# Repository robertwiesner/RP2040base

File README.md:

A small example for a RP2040 board with I2C (LCD display), LED blinking and some GPIOs

GPIO 0 - 3: LED

J4: 
GPIO6: GPIO/I2C1_SDA
GPIO7: GPIO/I2C1_SCL
GPIO8: GPIO/UART1_TX/I2C0_SDA/SPI1_RX
GPIO9: GPIO/UART1_RX/I2C0_SCL/SPI1_CSn
GPIO10: GPIO/I2C1_SDA/SPI1_SCK
GPIO11: GPIO/I2C1_SCL/SPI1_TX
GPIO12: GPIO/UART0_TX/I2C0_SDA/SPI1_RX
GPIO13: GPIO/UART0_RX/I2C0_SCL/SPI1_CSn

J3:
I2C0, GND, and 3.3V

HTTP Links and cloning:
* https://github.com/raspberrypi/picotool
* https://github.com/raspberrypi/pico-sdk
* https://github.com/raspberrypi/pico-extras

| End Symb |  |
| --- | --- |
| PICO_SDK_PATH | point to <path>/pico-sdk |
| PICO_EXTRAS_PATH | point to <path>/pico-extras |

Clone the pico repositories:
* https://github.com/raspberrypi/pico-sdk.git
* https://github.com/raspberrypi/pico-extras.git
* Install the picotool repository

How to build:
* First time:
 * make build directory in the source directory: mkdir build
 * chdir build
 * cmake ..
* every time
 * Change into build directory
 * Start build using "make"
 * install to pico: picotool load test.uf2 && picotool reboot

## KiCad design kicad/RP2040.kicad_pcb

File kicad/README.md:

This directory conteains the schematics and layout data for the C example program.

About the board:
1. Using a USB type C connector for power and USB 2.0 connection
2. I2C connector for LEC display
3. 4 * ANALOG input with 1:10 power divider for the RP2040 ADC input
4. Accessible GPIO 6 - 13
5. 2*5V (USB) and 2*3.3V connector
6. GPIO 0-3 connected to LED
7. 10-pin, 1.27mm SWD connector

The Part numbers in the schemetaics match the JLCPCB (not sponsered) order code.

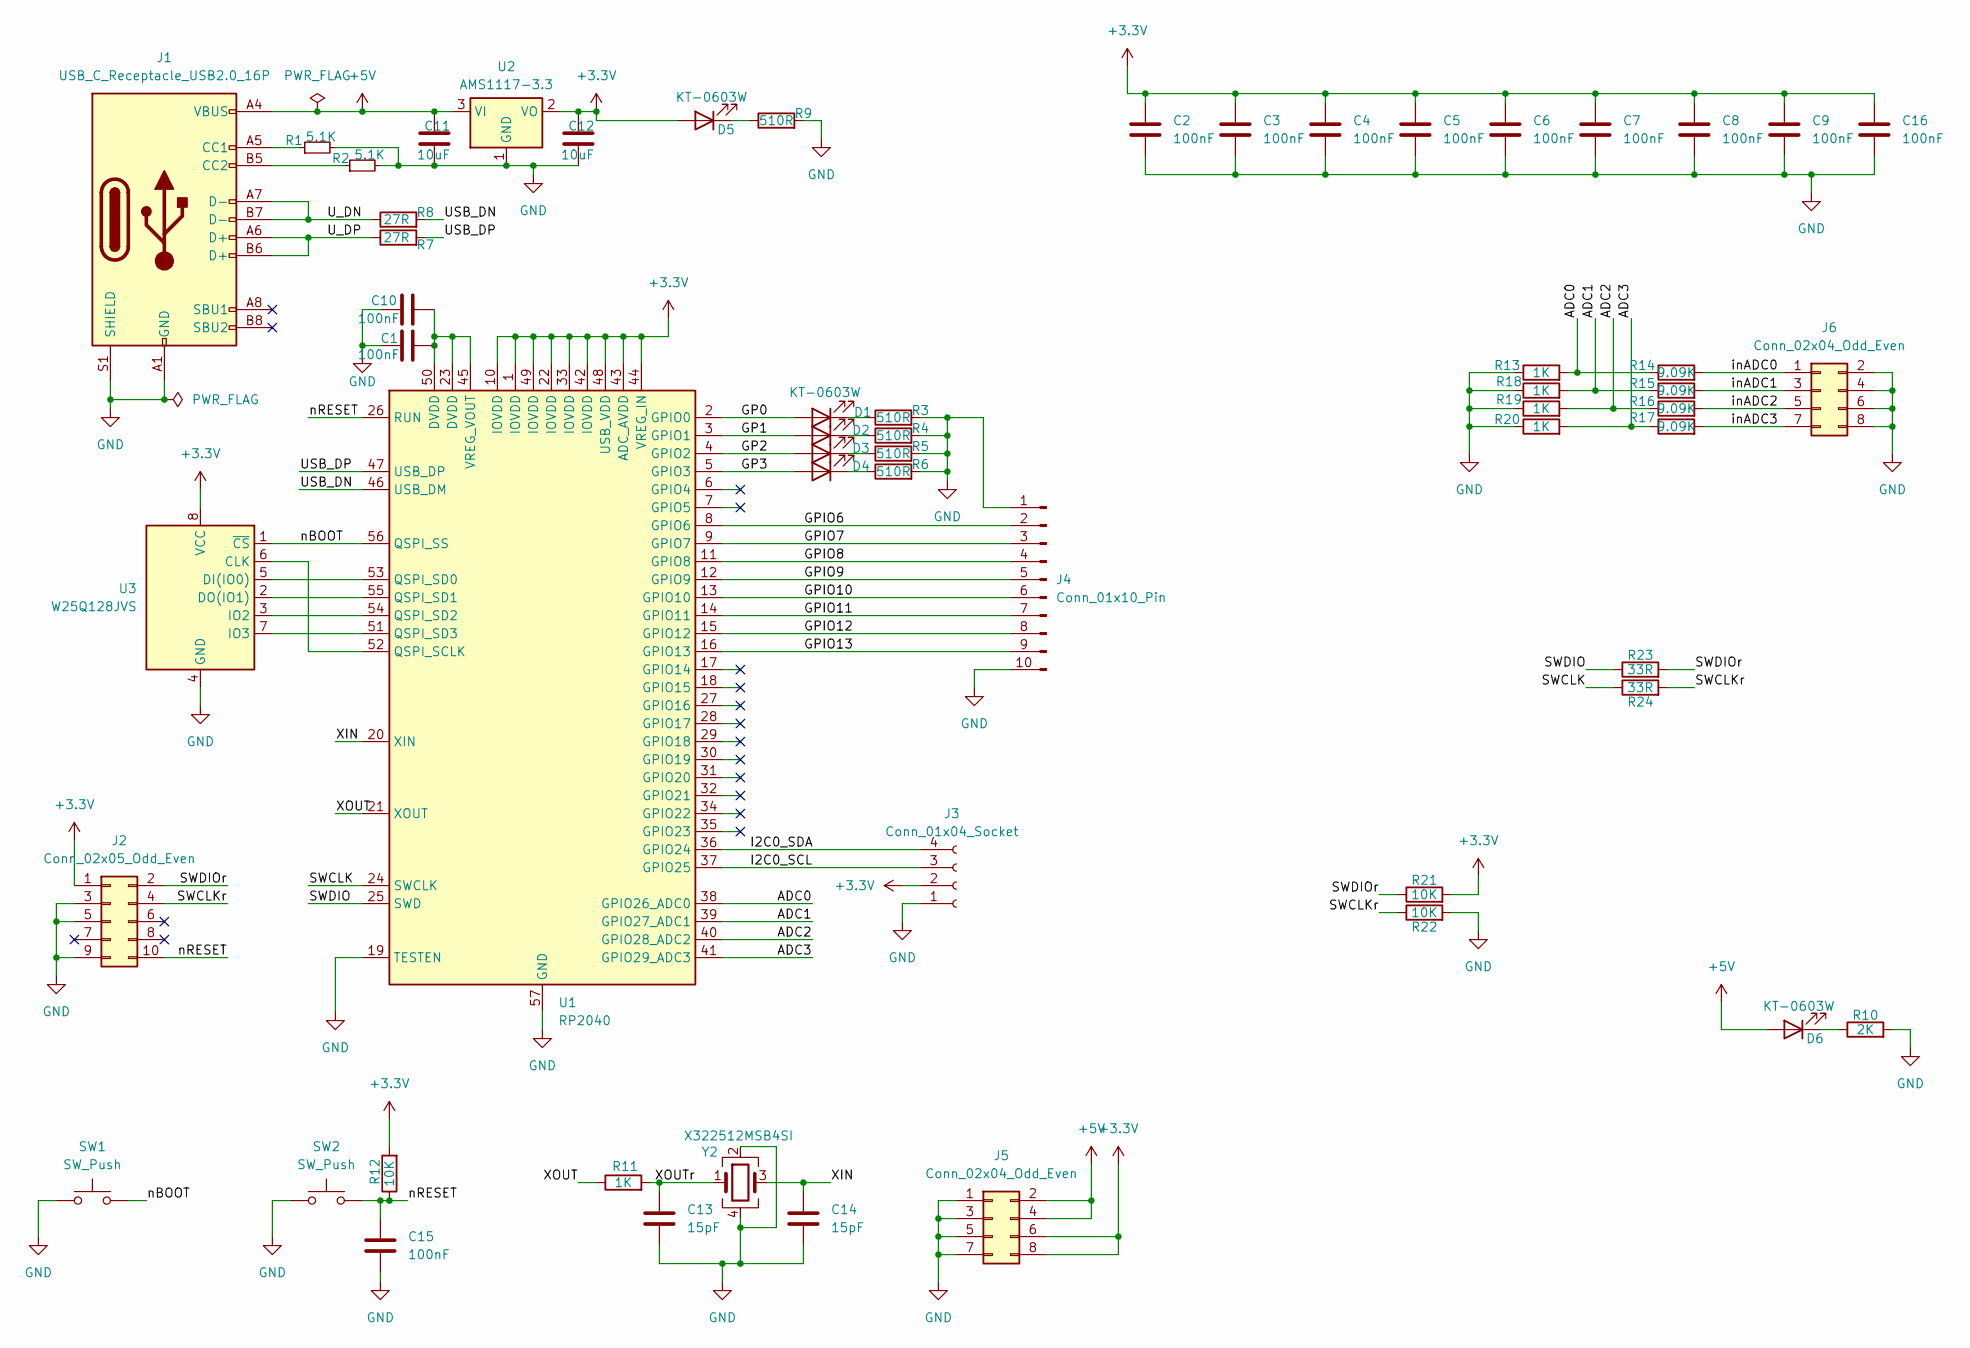
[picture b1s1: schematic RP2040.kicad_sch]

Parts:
C1, C2, C3, C4, C5, C6, C7, C8, C9, C10, C15, C16: 100nF; C_0402_1005Metric
C11, C12: 10uF; C_0603_1608Metric; LCSC C19702
C13, C14: 15pF; C_0402_1005Metric
D1, D2, D3, D4, D5, D6: KT-0603W; LED_0603_1608Metric
J1: USB_C_Receptacle_USB2.0_16P; USB_C_Receptacle_G-Switch_GT-USB-7010ASV
J2: Conn_02x05_Odd_Even; PinHeader_2x05_P1.27mm_Vertical_SMD; LCSC C5160761
J3: Conn_01x04_Socket; PinSocket_1x04_P2.54mm_Vertical
J4: Conn_01x10_Pin; PinSocket_1x10_P2.54mm_Vertical
J5, J6: Conn_02x04_Odd_Even; PinHeader_2x04_P2.54mm_Vertical
R1, R2: 5.1K; R_0402_1005Metric
R3, R4, R5, R6, R9: 510R; R_0402_1005Metric
R7, R8: 27R; R_0402_1005Metric
R10: 2K; R_0402_1005Metric
R11, R13, R18, R19, R20: 1K; R_0402_1005Metric
R12, R21, R22: 10K; R_0402_1005Metric
R14, R15, R16, R17: 9.09K; R_0402_1005Metric
R23, R24: 33R; R_0402_1005Metric
SW1, SW2: SW_Push; SW_Push_1P1T_XKB_TS-1187A
U1: RP2040; QFN-56-1EP_7x7mm_P0.4mm_EP3.2x3.2mm_ThermalVias
U2: AMS1117-3.3; SOT-223
U3: W25Q128JVS; SOIC-8_5.23x5.23mm_P1.27mm; LCSC C97521
Y2: X322512MSB4SI; Crystal_SMD_3225-4Pin_3.2x2.5mm; LCSC C9002

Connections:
+3.3V: C2.1, C3.1, C4.1, C5.1, C6.1, C7.1, C8.1, C9.1, C12.1, C16.1, D5.2 (A), J2.1, J3.2, J5.6, J5.8, R12.2, R21.2, U1.1 (IOVDD), U1.10 (IOVDD), U1.22 (IOVDD), U1.33 (IOVDD), U1.42 (IOVDD), U1.43 (ADC_AVDD), U1.44 (VREG_IN), U1.48 (USB_VDD), U1.49 (IOVDD), U2.2 (VO), U3.8 (VCC)
+5V: C11.1, D6.2 (A), J1.A4 (VBUS), J1.A9 (VBUS), J1.B4 (VBUS), J1.B9 (VBUS), J5.2, J5.4, U2.3 (VI)
/ADC0: R13.2, R14.1, U1.38 (GPIO26_ADC0)
/ADC1: R15.1, R18.2, U1.39 (GPIO27_ADC1)
/ADC2: R16.1, R19.2, U1.40 (GPIO28_ADC2)
/ADC3: R17.1, R20.2, U1.41 (GPIO29_ADC3)
/GP0: D1.2 (A), U1.2 (GPIO0)
/GP1: D2.2 (A), U1.3 (GPIO1)
/GP2: D3.2 (A), U1.4 (GPIO2)
/GP3: D4.2 (A), U1.5 (GPIO3)
/GPIO6: J4.2, U1.8 (GPIO6)
/GPIO7: J4.3, U1.9 (GPIO7)
/GPIO8: J4.4, U1.11 (GPIO8)
/GPIO9: J4.5, U1.12 (GPIO9)
/GPIO10: J4.6, U1.13 (GPIO10)
/GPIO11: J4.7, U1.14 (GPIO11)
/GPIO12: J4.8, U1.15 (GPIO12)
/GPIO13: J4.9, U1.16 (GPIO13)
/I2C0_SCL: J3.3, U1.37 (GPIO25)
/I2C0_SDA: J3.4, U1.36 (GPIO24)
/SWCLK: R24.1, U1.24 (SWCLK)
/SWCLKr: J2.4, R22.1, R24.2
/SWDIO: R23.1, U1.25 (SWD)
/SWDIOr: J2.2, R21.1, R23.2
/USB_DN: R8.2, U1.46 (USB_DM)
/USB_DP: R7.2, U1.47 (USB_DP)
/U_DN: J1.A7 (D-), J1.B7 (D-), R8.1
/U_DP: J1.A6 (D+), J1.B6 (D+), R7.1
/XIN: C14.1, U1.20 (XIN), Y2.3
/XOUT: R11.1, U1.21 (XOUT)
/XOUTr: C13.1, R11.2, Y2.1
/inADC0: J6.1, R14.2
/inADC1: J6.3, R15.2
/inADC2: J6.5, R16.2
/inADC3: J6.7, R17.2
/nBOOT: SW1.2, U1.56 (QSPI_SS), U3.1 (~CS)
/nRESET: C15.1, J2.10, R12.1, SW2.2, U1.26 (RUN)
GND: C1.2, C2.2, C3.2, C4.2, C5.2, C6.2, C7.2, C8.2, C9.2, C10.2, C11.2, C12.2, C13.2, C14.2, C15.2, C16.2, J1.A1 (GND), J1.A12 (GND), J1.B1 (GND), J1.B12 (GND), J1.S1 (SHIELD), J2.3, J2.5, J2.9, J3.1, J4.1, J4.10, J5.1, J5.3, J5.5, J5.7, J6.2, J6.4, J6.6, J6.8, R1.2, R2.2, R3.2, R4.2, R5.2, R6.2, R9.2, R10.2, R13.1, R18.1, R19.1, R20.1, R22.2, SW1.1, SW2.1, U1.19 (TESTEN), U1.57 (GND), U2.1 (GND), U3.4 (GND), Y2.2, Y2.4
unnamed: D1.1 (K), R3.1
unnamed: D2.1 (K), R4.1
unnamed: D3.1 (K), R5.1
unnamed: D4.1 (K), R6.1
unnamed: D5.1 (K), R9.1
unnamed: D6.1 (K), R10.1
unnamed: J1.A5 (CC1), R1.1
unnamed: J1.B5 (CC2), R2.1
unnamed: U1.52 (QSPI_SCLK), U3.6 (CLK)
unnamed: U1.53 (QSPI_SD0), U3.5 (DI(IO0))
unnamed: U1.55 (QSPI_SD1), U3.2 (DO(IO1))
unnamed: U1.54 (QSPI_SD2), U3.3 (IO2)
unnamed: U1.51 (QSPI_SD3), U3.7 (IO3)
unnamed: C1.1, C10.1, U1.23 (DVDD), U1.45 (VREG_VOUT), U1.50 (DVDD)

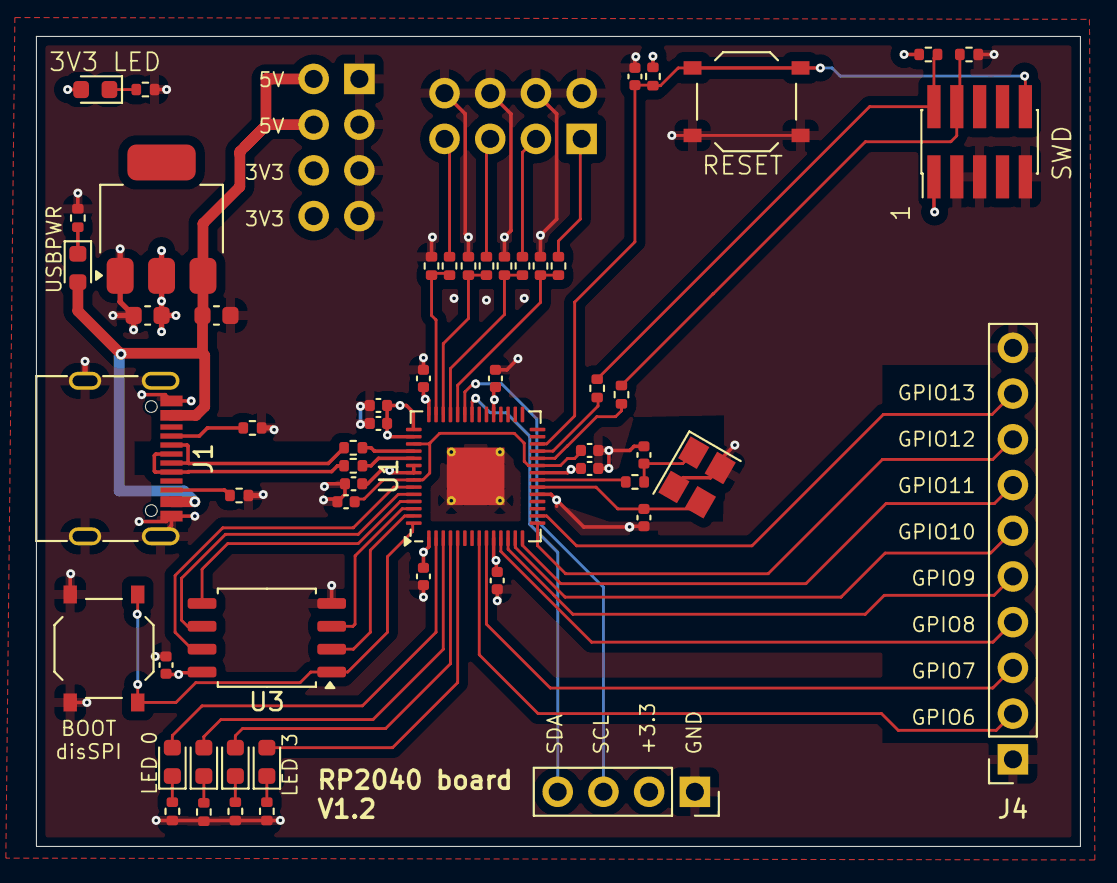
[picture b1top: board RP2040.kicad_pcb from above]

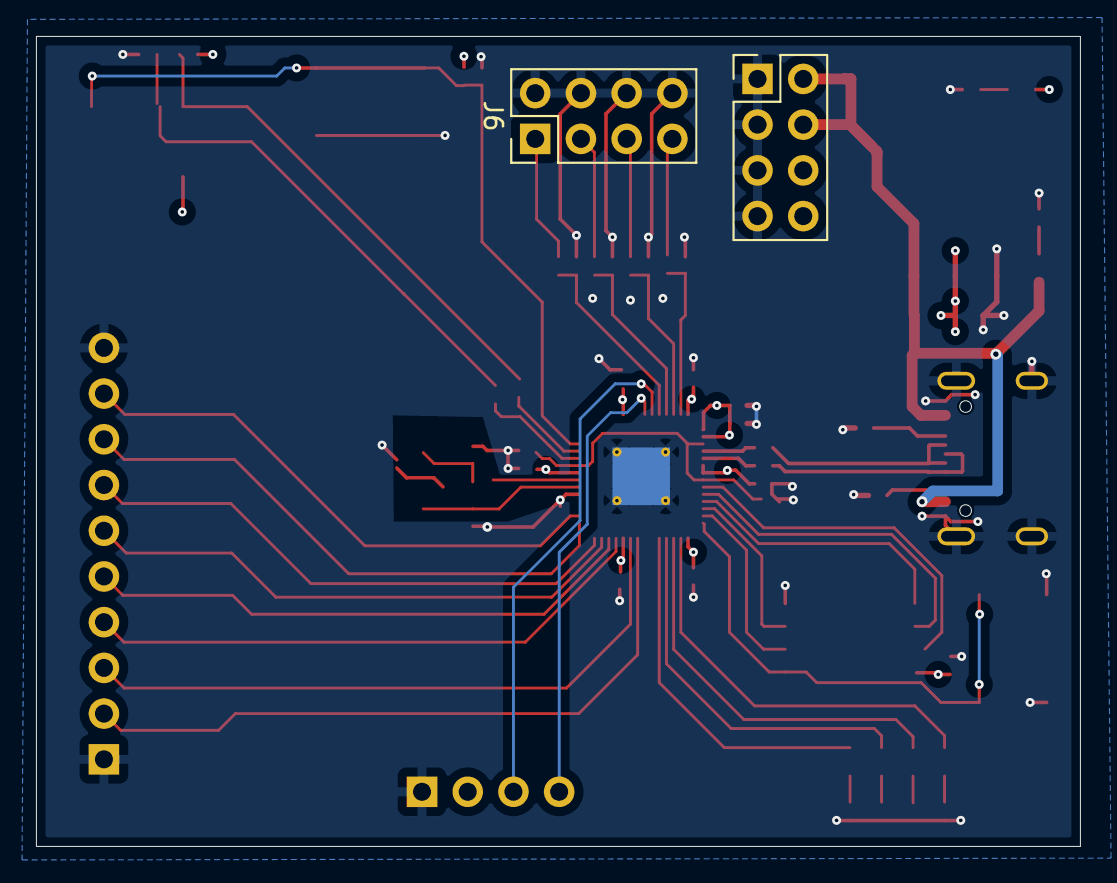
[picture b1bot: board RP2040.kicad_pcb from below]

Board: 4 copper layers, 58.0 x 45.0 mm, 58 parts (2 on the bottom side), 52 nets.

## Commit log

2025-02-19 Initial RP2040 base programming
2025-02-19 Create README.md
    Initial commit
2025-02-19 Add files via upload
    Initial commit.
2025-02-19 Update README.md
    Add PCB description
2025-02-19 Update README.md
    Added the GPIO usage
2025-02-19 Update README.md
    Add additional build instructions
2025-02-19 Update README.md
    Add web link
